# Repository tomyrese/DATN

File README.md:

# ĐỒ ÁN TỐT NGHIỆP: BO MẠCH CARRIER ROBOT 4WD CHO RASPBERRY PI 4 (CHUẨN 1 LỚP)

Hệ thống thiết kế phần cứng điện tử và phần mềm điều khiển cho Robot tự hành 4 bánh (4WD) sử dụng vi máy tính **Raspberry Pi 4**, tích hợp mạch nguồn hạ áp XL4015, 2 mạch cầu H công suất TB6612FNG, cảm biến siêu âm HC-SR04 và module dò line TCRT5000.

Mạch in được thiết kế tối ưu hóa đặc biệt theo dạng **Phẳng 1 Lớp (Single-Sided Planar PCB)**: **100% đường mạch đi trên lớp đáy (`B.Cu`), không sử dụng via, không jumper chéo dây, không phủ mass đồng kín**.

---

## 1. THÔNG SỐ KỸ THUẬT PHẦN CỨNG & DRC

| Tiêu chuẩn / Thông số | Giá trị thiết kế | Ghi chú kỹ thuật |
| :--- | :--- | :--- |
| **Số lớp mạch (Layers)** | **1 lớp duy nhất (`B.Cu`)** | Toàn bộ đường mạch nằm ở mặt hàn dưới |
| **Via xuyên lớp** | **0 Via** | Không chuyển lớp |
| **Khoảng cách chân (Pitch)** | **2.54 mm (100 mil)** | Đồng bộ 100% cho tất cả header, connector, IC |
| **Điện trở cắm (Axial R)** | **7.62 mm ($3 \times 2.54\text{ mm}$)** | Chuẩn lưới 2.54mm |
| **Kích thước Pad đồng** | **$1.4\text{ mm} \times 1.4\text{ mm}$** | Tròn / Oval cho độ bám thiếc tối ưu |
| **Đường kính lỗ khoan (Drill)** | **0.8 mm** | 3.2 mm cho 4 lỗ ốc cố định khung M3 |
| **Độ rộng dây Nguồn (Power)** | **1.4 mm** | Dòng tải cao cho 4 động cơ và Pi 4 |
| **Độ rộng dây Tín hiệu (Signal)** | **1.0 mm** | Chống đứt đường in khi gia công thủ công / phay |
| **Khoảng hở cách điện (Clearance)** | **$\ge 0.5\text{ mm}$** | Đảm bảo an toàn gia công, không lo chạm chập |
| **KiCad DRC Violations** | **0 lỗi (Zero DRC Errors)** | Đã qua kiểm tra DRC chính thức trên KiCad 10 |

---

## 2. BẢNG QUY HOẠCH CHÂN GPIO RASPBERRY PI 4 (IDC 40-PIN)

Tất cả tín hiệu được quy hoạch đối xứng để đi dây 1 lớp không chéo nhau:

### Khối Động cơ Trái (Driver `U_TB1` - `J_M1` & `J_M2`):
- **`PWMA_L`**: Pin 3 -> **BCM GPIO 2** (Điều khiển tốc độ PWM kênh A & B nối song song)
- **`AIN2_L`**: Pin 5 -> **BCM GPIO 3** (Điều khiển chiều quay AIN2 & BIN2)
- **`AIN1_L`**: Pin 7 -> **BCM GPIO 4** (Điều khiển chiều quay AIN1 & BIN1)
- **`STBY_L`**: Pin 11 -> **BCM GPIO 17** (Chân Standby bật/tắt driver công suất)

### Khối Động cơ Phải (Driver `U_TB2` - `J_M3` & `J_M4`):
- **`PWMA_R`**: Pin 33 -> **BCM GPIO 13** (PWM kênh A & B)
- **`AIN2_R`**: Pin 35 -> **BCM GPIO 19** (Chiều quay AIN2 & BIN2)
- **`AIN1_R`**: Pin 37 -> **BCM GPIO 26** (Chiều quay AIN1 & BIN1)
- **`STBY_R`**: Pin 38 -> **BCM GPIO 20** (Standby bật/tắt driver)

### Khối Cảm biến & Nguồn:
- **Cảm biến Siêu âm Trái (`U_US1`)**: TRIG -> Pin 13 (GPIO 27), ECHO -> Pin 15 (GPIO 22)
- **Cảm biến Siêu âm Phải (`U_US2`)**: TRIG -> Pin 29 (GPIO 5), ECHO -> Pin 31 (GPIO 6)
- **Cảm biến Dò Line 3 Kênh (`U_LINE`)**: Line Trái -> Pin 19 (GPIO 10), Line Giữa -> Pin 21 (GPIO 9), Line Phải -> Pin 23 (GPIO 11)
- **Nguồn cấp Pi 4**: Pin 2, 4 -> Nối trực tiếp nguồn **`+5V_PI`** từ mạch Buck XL4015 5A

---

## 3. CẤU TRÚC DỰ ÁN

```
.
├── code/                                # Mã nguồn phần mềm điều khiển
│   ├── python/                          # Chương trình Python CLI điều khiển động cơ
│   │   ├── config.py                    # Cấu hình chân GPIO phần cứng
│   │   ├── motor_controller.py          # Lớp điều khiển TB6612 (hỗ trợ Pi & PC simulation)
│   │   ├── test_left_motors.py          # Kịch bản kiểm tra tự động & thủ công 2 bánh trái
│   │   └── requirements.txt             # Thư viện phụ thuộc cho Raspberry Pi OS
│   ├── website/                         # Giao diện Web điều khiển từ xa qua WiFi
│   │   ├── index.html                   # Cyber-Dashboard điều khiển cảm ứng
│   │   ├── style.css                    # Dark mode, glassmorphism cao cấp
│   │   ├── app.js                       # Logic gửi lệnh API & bắt phím nóng bàn phím
│   │   └── server.py                    # HTTP & REST API Server tích hợp
│   └── README.md                        # Hướng dẫn chi tiết vận hành code
├── constraints/                         # Tài liệu ràng buộc thiết kế & topo mạch 1 lớp
├── gerbers/                             # Tệp Gerber & Khoan lỗ sẵn sàng gửi xưởng gia công
├── libraries/                           # Thư viện Footprint & Ký hiệu Schematic KiCad
├── Pi4_Robot_Carrier_1Layer.kicad_pcb   # File thiết kế PCB KiCad chính thức (Chuẩn 1 Lớp)
├── Pi4_Robot_Carrier_1Layer.kicad_sch   # File sơ đồ nguyên lý KiCad
├── Pi4_Robot_Carrier_1Layer.pdf         # Bản vẽ in ấn PCB chất lượng cao (PDF)
├── Pi4_Robot_Carrier_1Layer.svg         # Bản vẽ vector PCB (SVG)
├── Pi4_Robot_Carrier_BOM.html           # Bảng kê danh mục linh kiện (HTML tương tác)
├── Pi4_Robot_Carrier_BOM.csv            # Bảng kê linh kiện (CSV)
└── Pi4_Robot_Carrier_Schematic.pdf      # Sơ đồ nguyên lý xuất PDF
```

---

## 4. HƯỚNG DẪN CHẠY PHẦN MỀM

### A. Kiểm tra phần cứng bằng Python CLI
```bash
cd code/python
python test_left_motors.py
```
- Chọn `1`: Chạy kịch bản tự động kiểm tra tiến, lùi, phanh dừng và gia tốc mượt.
- Chọn `2`: Điều khiển thủ công bằng bàn phím (`W`: tiến, `S`: lùi, `B`: phanh, `Space`: dừng, `+`/`-`: tốc độ).

### B. Điều khiển trực tuyến qua Web Dashboard
```bash
cd code/website
python server.py
```
Truy cập qua trình duyệt:
- Trên máy tính: `http://localhost:8080`
- Trên điện thoại thông minh: `http://<IP_RASPBERRY_PI>:8080`

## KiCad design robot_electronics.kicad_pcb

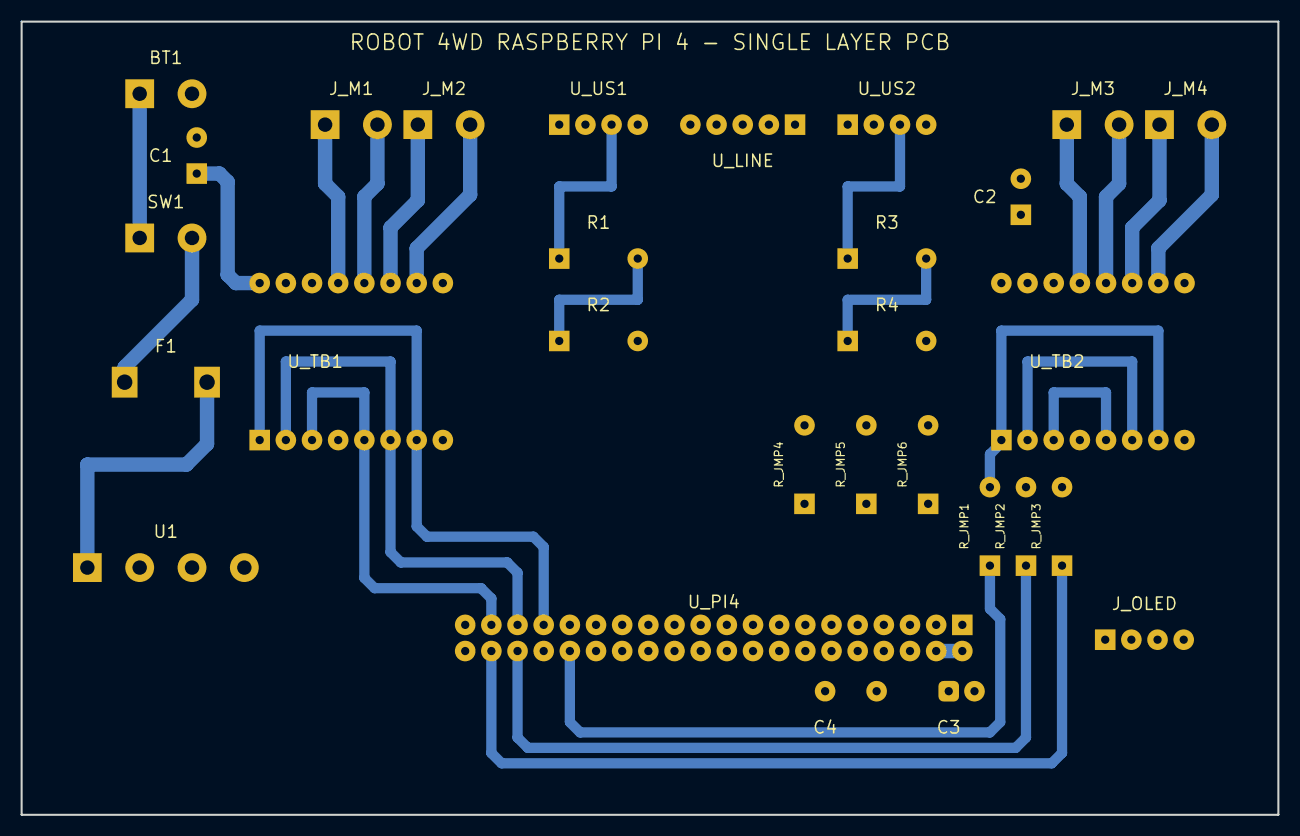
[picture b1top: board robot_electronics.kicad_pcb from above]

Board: 2 copper layers, 122.0 x 77.0 mm, 29 parts (0 on the bottom side), 34 nets.

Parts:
BT1: BATT_12V; TerminalBlock_Phoenix_MKDS-1,5-2-5.08
C1: C1; CP_Radial_D8.0mm_P3.50mm
C2: C2; CP_Radial_D8.0mm_P3.50mm
C3: C3; CP_Radial_D6.3mm_P2.50mm
C4: C4; C_Disc_D5.0mm_W2.5mm_P5.00mm
F1: FUSE_7.5A; Fuseholder_Blade_Mini_Keystone_3568
J_M1: M1_FL; TerminalBlock_Phoenix_MKDS-1,5-2-5.08
J_M2: M2_RL; TerminalBlock_Phoenix_MKDS-1,5-2-5.08
J_M3: M3_FR; TerminalBlock_Phoenix_MKDS-1,5-2-5.08
J_M4: M4_RR; TerminalBlock_Phoenix_MKDS-1,5-2-5.08
J_OLED: OLED; Sensor_OLED_1.3
R1: R1; R_Axial_DIN0207_L6.3mm_D2.5mm_P7.62mm_Horizontal
R2: R2; R_Axial_DIN0207_L6.3mm_D2.5mm_P7.62mm_Horizontal
R3: R3; R_Axial_DIN0207_L6.3mm_D2.5mm_P7.62mm_Horizontal
R4: R4; R_Axial_DIN0207_L6.3mm_D2.5mm_P7.62mm_Horizontal
R_JMP1: J1 (0R); R_Axial_DIN0207_L6.3mm_D2.5mm_P7.62mm_Horizontal
R_JMP2: J2 (0R); R_Axial_DIN0207_L6.3mm_D2.5mm_P7.62mm_Horizontal
R_JMP3: J3 (0R); R_Axial_DIN0207_L6.3mm_D2.5mm_P7.62mm_Horizontal
R_JMP4: J4 (0R); R_Axial_DIN0207_L6.3mm_D2.5mm_P7.62mm_Horizontal
R_JMP5: J5 (0R); R_Axial_DIN0207_L6.3mm_D2.5mm_P7.62mm_Horizontal
R_JMP6: J6 (0R); R_Axial_DIN0207_L6.3mm_D2.5mm_P7.62mm_Horizontal
SW1: SW_MAIN; TerminalBlock_Phoenix_MKDS-1,5-2-5.08
U1: XL4015_5V; TerminalBlock_Phoenix_MKDS-1,5-4-5.08
U_LINE: LINE_3CH; Sensor_Line_TCRT5000_3CH
U_PI4: Rasp_PI4; PinSocket_2x20_P2.54mm_Vertical
U_TB1: TB6612_L; Module_TB6612FNG_Breakout
U_TB2: TB6612_R; Module_TB6612FNG_Breakout
U_US1: US1_LEFT; Sensor_HC_SR04
U_US2: US2_RIGHT; Sensor_HC_SR04

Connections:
/+3V3_LOGIC: J_OLED.1, R_JMP5.1, R_JMP5.2, U_LINE.5, U_PI4.1, U_TB1.4, U_TB1.10, U_TB2.4, U_TB2.10
/+5V_PWR: C3.1, C4.1, R_JMP4.1, R_JMP4.2, U1.3, U_PI4.2, U_PI4.4, U_US1.1, U_US2.1
/AIN1_L: U_PI4.37, U_TB1.3, U_TB1.5
/AIN1_R: R_JMP2.2, U_TB2.3, U_TB2.5
/AIN2_L: U_PI4.35, U_TB1.2, U_TB1.6
/AIN2_R: R_JMP3.2, U_TB2.2, U_TB2.6
/BAT+: BT1.1, SW1.1
/ECHO_L: R1.2, R2.1, U_PI4.13
/ECHO_R: R3.2, R4.1, U_PI4.18
/FUSE_IN: F1.1, SW1.2
/GND: BT1.2, C1.2, C2.2, C3.2, C4.2, J_OLED.2, R2.2, R4.2, R_JMP6.1, R_JMP6.2, U1.2, U1.4, U_LINE.1, U_PI4.6, U_PI4.9, U_PI4.14, U_PI4.20, U_PI4.25, U_PI4.30, U_PI4.34, U_PI4.39, U_TB1.8, U_TB1.11, U_TB1.16, U_TB2.8, U_TB2.11, U_TB2.16, U_US1.4, U_US2.4
/I2C_SCL: J_OLED.3, U_PI4.5
/I2C_SDA: J_OLED.4, U_PI4.3
/LINE_C: U_LINE.3, U_PI4.21
/LINE_L: U_LINE.4, U_PI4.19
/LINE_R: U_LINE.2, U_PI4.23
/M1_A: J_M1.1, U_TB1.12
/M1_B: J_M1.2, U_TB1.13
/M2_A: J_M2.2, U_TB1.15
/M2_B: J_M2.1, U_TB1.14
/M3_A: J_M3.1, U_TB2.12
/M3_B: J_M3.2, U_TB2.13
/M4_A: J_M4.2, U_TB2.15
/M4_B: J_M4.1, U_TB2.14
/PWMA_L: U_PI4.33, U_TB1.1, U_TB1.7
/PWMA_R: R_JMP1.2, U_TB2.1, U_TB2.7
/TRIG_L: U_PI4.11, U_US1.2
/TRIG_R: U_PI4.16, U_US2.2
/VM_MOTOR: C1.1, C2.1, F1.2, U1.1, U_TB1.9, U_TB2.9
unnamed: R_JMP1.1, U_PI4.32
unnamed: R_JMP2.1, U_PI4.36
unnamed: R_JMP3.1, U_PI4.38
unnamed: R1.1, U_US1.3
unnamed: R3.1, U_US2.3

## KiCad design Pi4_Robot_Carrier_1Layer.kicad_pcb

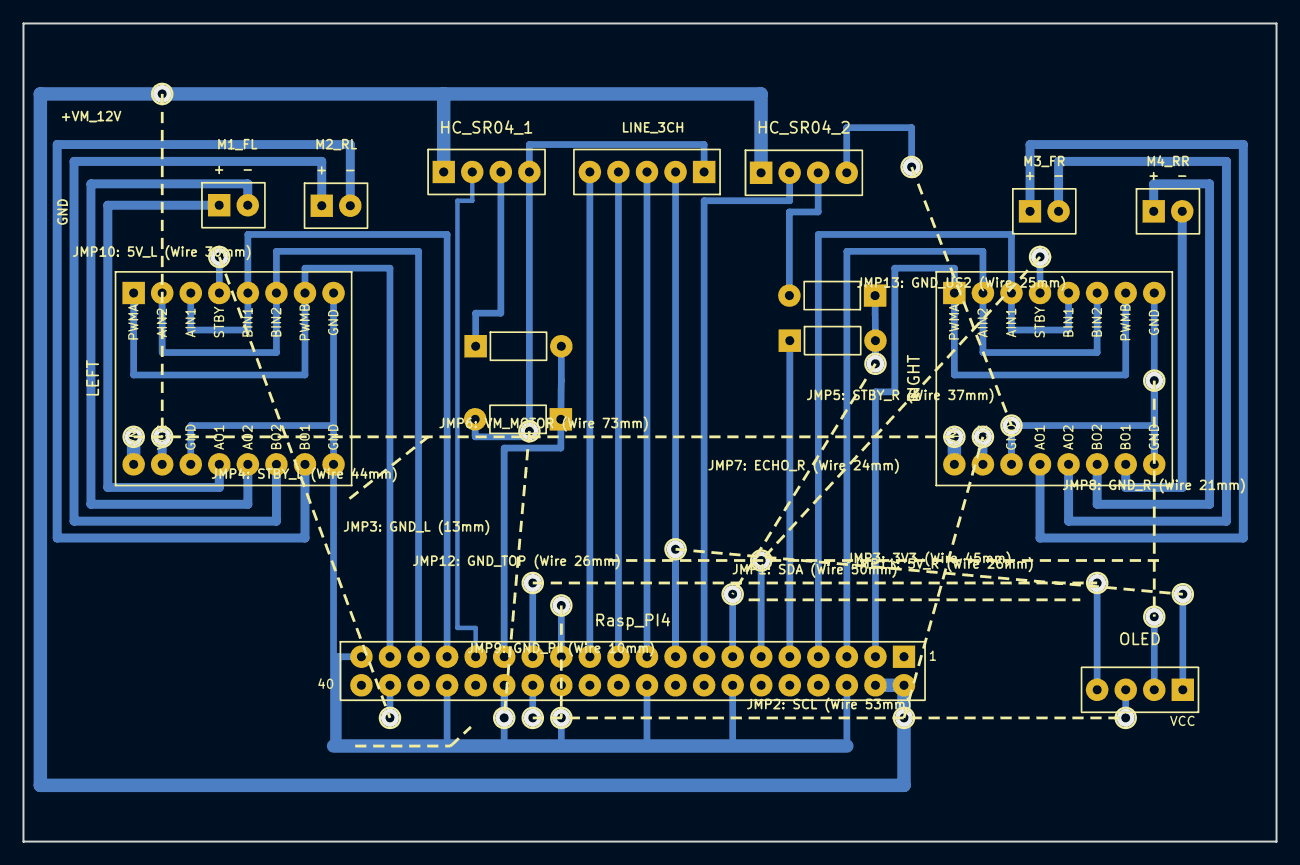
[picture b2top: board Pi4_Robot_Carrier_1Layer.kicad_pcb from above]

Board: 2 copper layers, 111.5 x 72.8 mm, 15 parts (0 on the bottom side), 31 nets.

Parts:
HC_SR04_1: HC_SR04_Left; Sensor_HC_SR04
HC_SR04_2: HC_SR04_Right; Sensor_HC_SR04
LEFT: TB6612_Left; Module_TB6612FNG_Breakout
MOTOR1: MOTOR_FL; TerminalBlock_Phoenix_MKDS-1,5-2-5.08
MOTOR2: MOTOR_RL; TerminalBlock_Phoenix_MKDS-1,5-2-5.08
MOTOR3: MOTOR_FR; TerminalBlock_Phoenix_MKDS-1,5-2-5.08
MOTOR4: MOTOR_RR; TerminalBlock_Phoenix_MKDS-1,5-2-5.08
OLED: OLED_1.3_I2C; Sensor_OLED_1.3
R1, R3: 1k; R_Axial_DIN0207_L6.3mm_D2.5mm_P7.62mm_Horizontal
R2, R4: 2k; R_Axial_DIN0207_L6.3mm_D2.5mm_P7.62mm_Horizontal
RIGHT: TB6612_Right; Module_TB6612FNG_Breakout
Rasp_PI4: Raspberry_Pi_4_40Pin; PinSocket_2x20_P2.54mm_Vertical
TCRT5000: TCRT5000_3CH; Sensor_Line_TCRT5000_3CH

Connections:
/+3V3_LOGIC: OLED.1, Rasp_PI4.17, TCRT5000.2
/+5V_PWR: HC_SR04_1.1, HC_SR04_2.1, LEFT.10, RIGHT.10, Rasp_PI4.2, Rasp_PI4.4
/AIN1_L: LEFT.3, LEFT.5, Rasp_PI4.33
/AIN1_R: RIGHT.3, RIGHT.5, Rasp_PI4.7
/AIN2_L: LEFT.2, LEFT.6, Rasp_PI4.35
/AIN2_R: RIGHT.2, RIGHT.6, Rasp_PI4.5
/ECHO_L: R1.2, R2.1, Rasp_PI4.29
/ECHO_R: R3.1, R4.2, Rasp_PI4.13
/I2C_SCL: OLED.3, Rasp_PI4.28
/I2C_SDA: OLED.4, Rasp_PI4.27
/LINE_C: Rasp_PI4.21, TCRT5000.4
/LINE_L: Rasp_PI4.19, TCRT5000.3
/LINE_R: Rasp_PI4.23, TCRT5000.5
/M1_A: LEFT.12, MOTOR1.1
/M1_B: LEFT.13, MOTOR1.2
/M2_A: LEFT.15, MOTOR2.2
/M2_B: LEFT.14, MOTOR2.1
/M3_A: MOTOR3.1, RIGHT.12
/M3_B: MOTOR3.2, RIGHT.13
/M4_A: MOTOR4.2, RIGHT.15
/M4_B: MOTOR4.1, RIGHT.14
/PWMA_L: LEFT.1, LEFT.7, Rasp_PI4.37
/PWMA_R: RIGHT.1, RIGHT.7, Rasp_PI4.3
/STBY_L: LEFT.4, Rasp_PI4.38
/STBY_R: RIGHT.4, Rasp_PI4.11
/TRIG_L: HC_SR04_1.2, Rasp_PI4.31
/TRIG_R: HC_SR04_2.2, Rasp_PI4.15
/VM_MOTOR: LEFT.9, RIGHT.9
GND: HC_SR04_1.4, HC_SR04_2.4, LEFT.8, LEFT.11, LEFT.16, OLED.2, R2.2, R4.1, RIGHT.8, RIGHT.11, RIGHT.16, Rasp_PI4.6, Rasp_PI4.9, Rasp_PI4.14, Rasp_PI4.20, Rasp_PI4.25, Rasp_PI4.30, Rasp_PI4.34, Rasp_PI4.39, TCRT5000.1
unnamed: HC_SR04_1.3, R1.1
unnamed: HC_SR04_2.3, R3.2

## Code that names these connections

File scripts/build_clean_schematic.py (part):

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                             'robot_electronics:TerminalBlock_Phoenix_MKDS-1,5-2-5.08',
                             ['60.96', '48.26', '0'], pins=['1', '2']))
wires_sexpr.append(add_wire([66.04, 48.26], [81.28, 48.26])) # SW1.2 to F1.1
labels_sexpr.append(add_label('FUSE_IN', [73.66, 48.26]))

symbols_sexpr.append(add_sym('robot_electronics:Fuse', 'F1', '7.5A_Blade',
                             'robot_electronics:Fuseholder_Blade_Mini_Keystone_3568',
                             ['86.36', '48.26', '0'], pins=['1', '2']))
labels_sexpr.append(add_label('VM_MOTOR', [91.44, 48.26]))    # F1.2 to VM_MOTOR

symbols_sexpr.append(add_sym('robot_electronics:XL4015_Buck_Module', 'U1', 'XL4015_Buck_5A',
                             'robot_electronics:TerminalBlock_Phoenix_MKDS-1,5-4-5.08',
                             ['137.16', '50.80', '0'], pins=['1', '2', '3', '4']))
labels_sexpr.append(add_label('VM_MOTOR', [116.84, 45.72], '180')) # Pin 1 IN+
labels_sexpr.append(add_label('GND', [116.84, 55.88], '180'))      # Pin 2 IN- (Star GND)
labels_sexpr.append(add_label('+5V_PWR', [157.48, 45.72]))         # Pin 3 OUT+
labels_sexpr.append(add_label('GND', [157.48, 55.88]))             # Pin 4 OUT- (Star GND)
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symbols_sexpr.append(add_sym('robot_electronics:C_Polarized', 'C1', '470uF_25V',
                             'robot_electronics:CP_Radial_D8.0mm_P3.50mm',
                             ['182.88', '50.80', '0'], pins=['1', '2']))
labels_sexpr.append(add_label('VM_MOTOR', [182.88, 45.72], '90'))
labels_sexpr.append(add_label('GND', [182.88, 55.88], '270'))

symbols_sexpr.append(add_sym('robot_electronics:C_Polarized', 'C2', '470uF_25V',
                             'robot_electronics:CP_Radial_D8.0mm_P3.50mm',
                             ['198.12', '50.80', '0'], pins=['1', '2']))
labels_sexpr.append(add_label('VM_MOTOR', [198.12, 45.72], '90'))
labels_sexpr.append(add_label('GND', [198.12, 55.88], '270'))

symbols_sexpr.append(add_sym('robot_electronics:C_Polarized', 'C3', '470uF_10V',
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symbols_sexpr.append(add_sym('robot_electronics:Module_TB6612FNG_Breakout', 'U_TB1', 'TB6612_Left',
                             'robot_electronics:Module_TB6612FNG_Breakout',
                             ['81.28', '127.00', '0'], pins=[str(i) for i in range(1, 17)]))
labels_sexpr.append(add_label('PWMA_L', [58.42, 109.22], '180'))
labels_sexpr.append(add_label('AIN2_L', [58.42, 114.30], '180'))
labels_sexpr.append(add_label('AIN1_L', [58.42, 119.38], '180'))
labels_sexpr.append(add_label('+3V3_LOGIC', [58.42, 124.46], '180')) # STBY -> 3.3V
labels_sexpr.append(add_label('AIN1_L', [58.42, 129.54], '180'))     # BIN1 -> AIN1
labels_sexpr.append(add_label('AIN2_L', [58.42, 134.62], '180'))     # BIN2 -> AIN2
labels_sexpr.append(add_label('PWMA_L', [58.42, 139.70], '180'))     # PWMB -> PWMA
labels_sexpr.append(add_label('GND', [58.42, 144.78], '180'))
labels_sexpr.append(add_label('VM_MOTOR', [104.14, 109.22]))
labels_sexpr.append(add_label('+3V3_LOGIC', [104.14, 114.30]))        # VCC -> 3.3V
labels_sexpr.append(add_label('GND', [104.14, 119.38]))
labels_sexpr.append(add_label('M1_A', [104.14, 124.46]))
labels_sexpr.append(add_label('M1_B', [104.14, 129.54]))
labels_sexpr.append(add_label('M2_B', [104.14, 134.62]))
labels_sexpr.append(add_label('M2_A', [104.14, 139.70]))
labels_sexpr.append(add_label('GND', [104.14, 144.78]))

symbols_sexpr.append(add_sym('robot_electronics:Conn_01x02', 'J_M1', 'MOTOR_FL',
                             'robot_electronics:TerminalBlock_Phoenix_MKDS-1,5-2-5.08',
                             ['132.08', '127.00', '0'], pins=['1', '2']))
labels_sexpr.append(add_label('M1_A', [127.00, 124.46], '180'))
labels_sexpr.append(add_label('M1_B', [127.00, 129.54], '180'))

symbols_sexpr.append(add_sym('robot_electronics:Conn_01x02', 'J_M2', 'MOTOR_RL',
                             'robot_electronics:TerminalBlock_Phoenix_MKDS-1,5-2-5.08',
                             ['132.08', '137.16', '0'], pins=['1', '2']))
labels_sexpr.append(add_label('M2_B', [127.00, 134.62], '180'))
labels_sexpr.append(add_label('M2_A', [127.00, 139.70], '180'))

# 3. TB6612 RIGHT & MOTORS
symbols_sexpr.append(add_sym('robot_electronics:Module_TB6612FNG_Breakout', 'U_TB2', 'TB6612_Right',
                             'robot_electronics:Module_TB6612FNG_Breakout',
                             ['299.72', '127.00', '0'], pins=[str(i) for i in range(1, 17)]))
labels_sexpr.append(add_label('PWMA_R', [276.86, 109.22], '180'))
labels_sexpr.append(add_label('AIN2_R', [276.86, 114.30], '180'))
labels_sexpr.append(add_label('AIN1_R', [276.86, 119.38], '180'))
labels_sexpr.append(add_label('+3V3_LOGIC', [276.86, 124.46], '180')) # STBY -> 3.3V
labels_sexpr.append(add_label('AIN1_R', [276.86, 129.54], '180'))     # BIN1 -> AIN1
labels_sexpr.append(add_label('AIN2_R', [276.86, 134.62], '180'))     # BIN2 -> AIN2
labels_sexpr.append(add_label('PWMA_R', [276.86, 139.70], '180'))     # PWMB -> PWMA
labels_sexpr.append(add_label('GND', [276.86, 144.78], '180'))
labels_sexpr.append(add_label('VM_MOTOR', [322.58, 109.22]))
labels_sexpr.append(add_label('+3V3_LOGIC', [322.58, 114.30]))        # VCC -> 3.3V
labels_sexpr.append(add_label('GND', [322.58, 119.38]))
labels_sexpr.append(add_label('M3_A', [322.58, 124.46]))
labels_sexpr.append(add_label('M3_B', [322.58, 129.54]))
labels_sexpr.append(add_label('M4_B', [322.58, 134.62]))
labels_sexpr.append(add_label('M4_A', [322.58, 139.70]))
labels_sexpr.append(add_label('GND', [322.58, 144.78]))

symbols_sexpr.append(add_sym('robot_electronics:Conn_01x02', 'J_M3', 'MOTOR_FR',
                             'robot_electronics:TerminalBlock_Phoenix_MKDS-1,5-2-5.08',
                             ['350.52', '127.00', '0'], pins=['1', '2']))
labels_sexpr.append(add_label('M3_A', [345.44, 124.46], '180'))
labels_sexpr.append(add_label('M3_B', [345.44, 129.54], '180'))

symbols_sexpr.append(add_sym('robot_electronics:Conn_01x02', 'J_M4', 'MOTOR_RR',
                             'robot_electronics:TerminalBlock_Phoenix_MKDS-1,5-2-5.08',
                             ['350.52', '137.16', '0'], pins=['1', '2']))
labels_sexpr.append(add_label('M4_B', [345.44, 134.62], '180'))
labels_sexpr.append(add_label('M4_A', [345.44, 139.70], '180'))

# 4. SENSORS (US1, US2, TCRT5000, OLED)
# US1
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                             'robot_electronics:Sensor_HC_SR04',
                             ['76.20', '190.50', '0'], pins=['1', '2', '3', '4']))
labels_sexpr.append(add_label('+5V_PWR', [58.42, 185.42], '180'))
labels_sexpr.append(add_label('TRIG_L', [58.42, 193.04], '180'))
wires_sexpr.append(add_wire([93.98, 193.04], [109.22, 193.04])) # ECHO to R1.1
labels_sexpr.append(add_label('GND', [93.98, 198.12]))

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                             'robot_electronics:R_Axial_DIN0207_L6.3mm_D2.5mm_P7.62mm_Horizontal',
                             ['114.30', '193.04', '90'], pins=['1', '2']))
wires_sexpr.append(add_wire([119.38, 193.04], [119.38, 200.66])) # R1.2 to R2.1
labels_sexpr.append(add_label('ECHO_L', [119.38, 193.04]))

symbols_sexpr.append(add_sym('robot_electronics:R', 'R2', '2k',
                             'robot_electronics:R_Axial_DIN0207_L6.3mm_D2.5mm_P7.62mm_Horizontal',
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                             'robot_electronics:Sensor_HC_SR04',
                             ['299.72', '190.50', '0'], pins=['1', '2', '3', '4']))
labels_sexpr.append(add_label('+5V_PWR', [281.94, 185.42], '180'))
labels_sexpr.append(add_label('TRIG_R', [281.94, 193.04], '180'))
wires_sexpr.append(add_wire([317.50, 193.04], [332.74, 193.04])) # ECHO to R3.1
labels_sexpr.append(add_label('GND', [317.50, 198.12]))

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                             'robot_electronics:R_Axial_DIN0207_L6.3mm_D2.5mm_P7.62mm_Horizontal',
                             ['337.82', '193.04', '90'], pins=['1', '2']))
wires_sexpr.append(add_wire([342.90, 193.04], [342.90, 200.66])) # R3.2 to R4.1
labels_sexpr.append(add_label('ECHO_R', [342.90, 193.04]))

symbols_sexpr.append(add_sym('robot_electronics:R', 'R4', '2k',
                             'robot_electronics:R_Axial_DIN0207_L6.3mm_D2.5mm_P7.62mm_Horizontal',
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                             ['187.96', '182.88', '0'], pins=['1', '2', '3', '4', '5']))
labels_sexpr.append(add_label('GND', [170.18, 190.50], '180'))
labels_sexpr.append(add_label('+3V3_LOGIC', [170.18, 175.26], '180'))
labels_sexpr.append(add_label('LINE_R', [205.74, 177.80]))
labels_sexpr.append(add_label('LINE_C', [205.74, 182.88]))
labels_sexpr.append(add_label('LINE_L', [205.74, 187.96]))

# OLED 1.3"
symbols_sexpr.append(add_sym('robot_electronics:Display_OLED_1.3_I2C', 'J_OLED', 'OLED_1.3_I2C',
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                             ['314.96', '256.54', '0'], pins=['1', '2', '3', '4']))
labels_sexpr.append(add_label('+3V3_LOGIC', [299.72, 252.73], '180'))
labels_sexpr.append(add_label('GND', [299.72, 260.35], '180'))
labels_sexpr.append(add_label('I2C_SCL', [330.20, 252.73]))
labels_sexpr.append(add_label('I2C_SDA', [330.20, 260.35]))

# 5. ZERO-OHM JUMPERS R_JMP1..R_JMP6
symbols_sexpr.append(add_sym('robot_electronics:R', 'R_JMP1', '0R',
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
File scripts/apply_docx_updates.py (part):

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        ("Pin 02", "+5V_PI_1", "-", "Power In", "5.0V DC", "Nguồn 5V từ module Buck XL4015 cấp vào nuôi Raspberry Pi 4"),
        ("Pin 04", "+5V_PI_2", "-", "Power In", "5.0V DC", "Nguồn 5V từ module Buck XL4015 cấp vào nuôi Pi 4 (nối song song Pin 2)"),
        ("Pin 06", "GND", "-", "Ground", "0V", "Mass chung toàn hệ thống"),
        ("Pin 03", "PWMA_L", "GPIO 2", "Output", "3.3V LVTTL", "Xung PWM điều khiển tốc độ cụm động cơ Trái (Driver TB6612 #1)"),
        ("Pin 05", "AIN2_L", "GPIO 3", "Output", "3.3V LVTTL", "Tín hiệu logic điều khiển chiều quay động cơ Trái (kết nối AIN2/BIN2)"),
        ("Pin 07", "AIN1_L", "GPIO 4", "Output", "3.3V LVTTL", "Tín hiệu logic điều khiển chiều quay động cơ Trái (kết nối AIN1/BIN1)"),
        ("Pin 11", "STBY_L", "GPIO 17", "Output", "3.3V LVTTL", "Chân kích hoạt Standby Driver TB6612 Trái (HIGH = Enable)"),
        ("Pin 13", "TRIG_L", "GPIO 27", "Output", "3.3V LVTTL", "Phát xung siêu âm kích hoạt đo cự ly (HC-SR04 Trái)"),
        ("Pin 15", "ECHO_L", "GPIO 22", "Input", "3.3V LVTTL", "Nhận xung phản hồi cảm biến Trái (qua cầu phân áp 1kΩ / 2kΩ)"),
        ("Pin 17", "3.3V Power", "-", "Power Out", "3.3V DC", "Nguồn logic 3.3V dự phòng"),
        ("Pin 19", "LINE_L", "GPIO 10", "Input", "3.3V LVTTL", "Tín hiệu cảm biến dò đường (Line Sensor) kênh Trái"),
        ("Pin 21", "LINE_C", "GPIO 9", "Input", "3.3V LVTTL", "Tín hiệu cảm biến dò đường (Line Sensor) kênh Giữa"),
        ("Pin 23", "LINE_R", "GPIO 11", "Input", "3.3V LVTTL", "Tín hiệu cảm biến dò đường (Line Sensor) kênh Phải"),
        ("Pin 25", "GND", "-", "Ground", "0V", "Mass cảm biến line"),
        ("Pin 27", "I2C_SDA", "GPIO 0/2", "Bidirectional", "3.3V Logic", "Đường truyền dữ liệu I²C SDA giao tiếp Màn hình OLED 1.3 inch"),
        ("Pin 28", "I2C_SCL", "GPIO 1/3", "Output", "3.3V Logic", "Đường xung nhịp I²C SCL giao tiếp Màn hình OLED 1.3 inch"),
        ("Pin 29", "TRIG_R", "GPIO 5", "Output", "3.3V LVTTL", "Phát xung siêu âm kích hoạt đo cự ly (HC-SR04 Phải)"),
        ("Pin 31", "ECHO_R", "GPIO 6", "Input", "3.3V LVTTL", "Nhận xung phản hồi cảm biến Phải (qua cầu phân áp 1kΩ / 2kΩ)"),
        ("Pin 33", "PWMA_R", "GPIO 13", "Output", "3.3V LVTTL", "Xung PWM điều khiển tốc độ cụm động cơ Phải (Driver TB6612 #2)"),
        ("Pin 35", "AIN2_R", "GPIO 19", "Output", "3.3V LVTTL", "Tín hiệu logic điều khiển chiều quay động cơ Phải (kết nối AIN2/BIN2)"),
        ("Pin 37", "AIN1_R", "GPIO 26", "Output", "3.3V LVTTL", "Tín hiệu logic điều khiển chiều quay động cơ Phải (kết nối AIN1/BIN1)"),
        ("Pin 38", "STBY_R", "GPIO 20", "Output", "3.3V LVTTL", "Chân kích hoạt Standby Driver TB6612 Phải (HIGH = Enable)"),
        ("Pin 39", "GND", "-", "Ground", "0V", "Mass chung toàn hệ thống"),
    ]

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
